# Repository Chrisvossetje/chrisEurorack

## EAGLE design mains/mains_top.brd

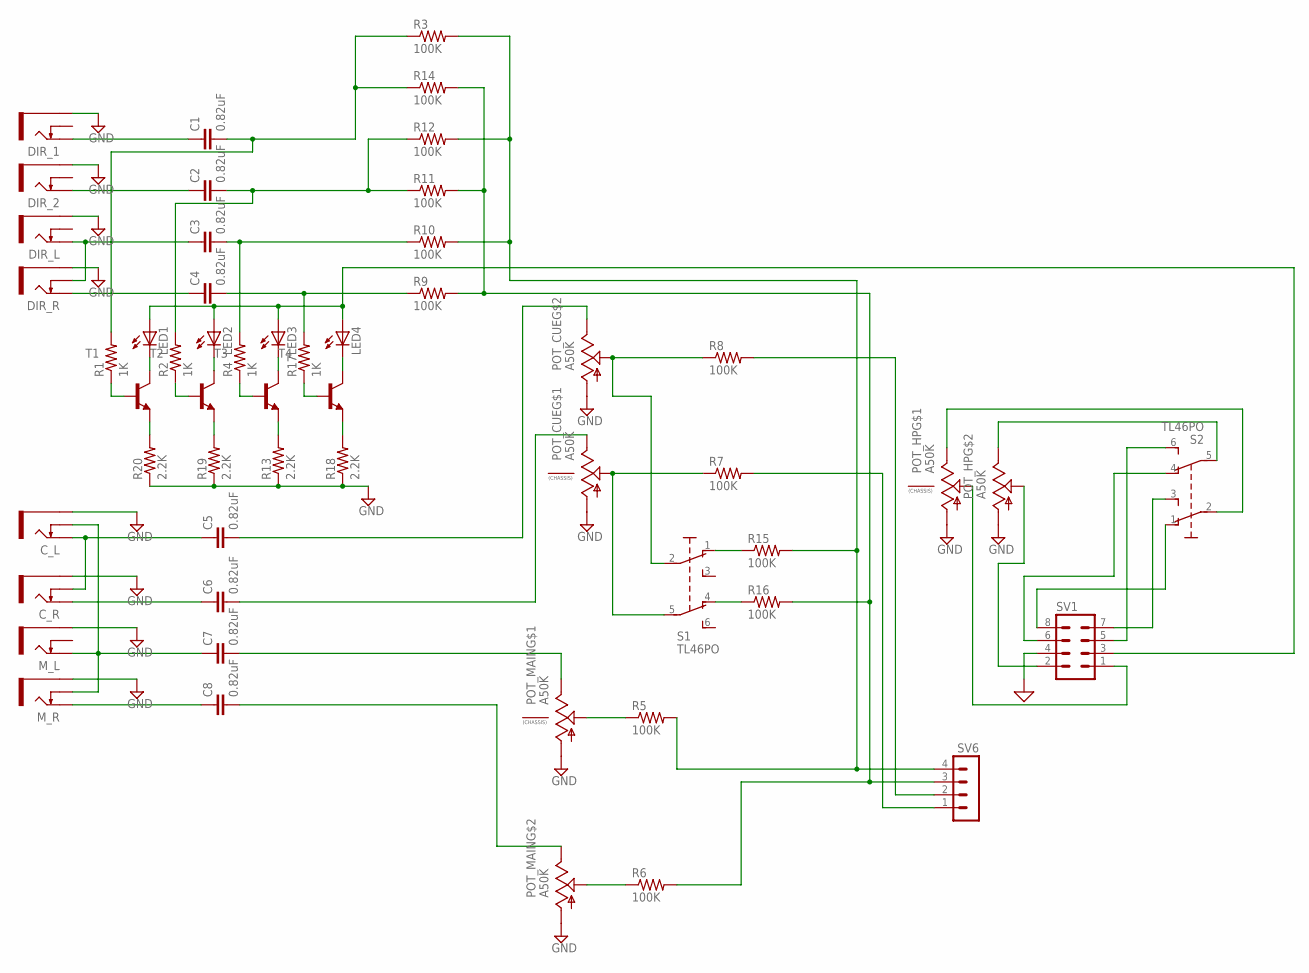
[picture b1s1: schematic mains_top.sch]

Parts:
C1, C2, C3, C4, C5, C6, C7, C8: 0.82uF; C0603K
C_L: THONKICONNNEW; WQP-PJ301M-12_JACK
C_R: THONKICONNNEW; WQP-PJ301M-12_JACK
DIR_1, DIR_2: THONKICONNNEW; WQP-PJ301M-12_JACK
DIR_L: THONKICONNNEW; WQP-PJ301M-12_JACK
DIR_R: THONKICONNNEW; WQP-PJ301M-12_JACK
LED1, LED2, LED3, LED4: LED3MM
M_L: THONKICONNNEW; WQP-PJ301M-12_JACK
M_R: THONKICONNNEW; WQP-PJ301M-12_JACK
POT_CUE: A50K; DUAL_9MM_SNAP-IN_POT
POT_HP: A50K; DUAL_9MM_SNAP-IN_POT
POT_MAIN: A50K; DUAL_9MM_SNAP-IN_POT
R1, R2, R4, R17: 1K; R0603
R3, R5, R6, R7, R8, R9, R10, R11, R12, R14, R15, R16: 100K; R0603
R13, R18, R19, R20: 2.2K; R0603
S1, S2: TL46PO; TL4XPO
SV1: MA04-2
SV6: MA04-1
T1, T2, T3, T4: MMBT3904LT1-NPN-SOT23-BEC; SOT23-BEC

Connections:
GND: C_L.P$3_SLEEVE (SLEEVE), C_R.P$3_SLEEVE (SLEEVE), DIR_1.P$3_SLEEVE (SLEEVE), DIR_2.P$3_SLEEVE (SLEEVE), DIR_L.P$3_SLEEVE (SLEEVE), DIR_R.P$3_SLEEVE (SLEEVE), M_L.P$3_SLEEVE (SLEEVE), M_R.P$3_SLEEVE (SLEEVE), POT_CUE.1 (A), POT_CUE.1B (A), POT_HP.1 (A), POT_HP.1B (A), POT_MAIN.1 (A), POT_MAIN.1B (A), R13.1, R18.1, R19.1, R20.1, SV1.4
unnamed: S2.1 (O), SV1.8
unnamed: R20.2, T1.E
unnamed: R19.2, T2.E
unnamed: S2.4 (O1), SV1.6
unnamed: LED1.K (C), T1.C
unnamed: POT_HP.2B (S), SV1.2
unnamed: C7.1, C_L.P$2_SWITCH (SWITCH), M_L.P$1_TIP (TIP), M_R.P$2_SWITCH (SWITCH)
unnamed: POT_HP.2 (S), SV1.1
unnamed: R1.1, T1.B
unnamed: R2.1, T2.B
unnamed: LED1.A, LED2.A, LED3.A, LED4.A, SV1.3
unnamed: C8.2, POT_MAIN.3B (E)
unnamed: C3.2, R4.2, R10.1
unnamed: C4.2, R9.1, R17.2
unnamed: C2.1, DIR_2.P$1_TIP (TIP)
unnamed: C1.1, DIR_1.P$1_TIP (TIP)
unnamed: C6.2, POT_CUE.3 (E)
unnamed: C5.2, POT_CUE.3B (E)
unnamed: POT_CUE.2B (S), R8.1, S1.2
unnamed: LED3.K (C), T3.C
unnamed: POT_MAIN.2 (S), R5.1
unnamed: POT_MAIN.2B (S), R6.1
unnamed: S2.6 (S1), SV1.5
unnamed: LED4.K (C), T4.C
unnamed: S2.3 (S), SV1.7
unnamed: R17.1, T4.B
unnamed: POT_HP.3B (E), S2.5 (P1)
unnamed: POT_HP.3 (E), S2.2
unnamed: R15.1, S1.1 (O)
unnamed: R16.1, S1.4 (O1)
unnamed: R6.2, R9.2, R11.2, R14.2, R16.2, SV6.3
unnamed: R4.1, T3.B
unnamed: R7.2, SV6.1
unnamed: R8.2, SV6.2
unnamed: LED2.K (C), T2.C
unnamed: R13.2, T3.E
unnamed: R18.2, T4.E
unnamed: POT_CUE.2 (S), R7.1, S1.5 (P1)
unnamed: C3.1, DIR_L.P$1_TIP (TIP), DIR_R.P$2_SWITCH (SWITCH)
unnamed: C2.2, R2.2, R11.1, R12.1
unnamed: C1.2, R1.2, R3.1, R14.1
unnamed: C4.1, DIR_R.P$1_TIP (TIP)
unnamed: C7.2, POT_MAIN.3 (E)
unnamed: C5.1, C_L.P$1_TIP (TIP), C_R.P$2_SWITCH (SWITCH)
unnamed: C8.1, M_R.P$1_TIP (TIP)
unnamed: C6.1, C_R.P$1_TIP (TIP)
unnamed: R3.2, R5.2, R10.2, R12.2, R15.2, SV6.4

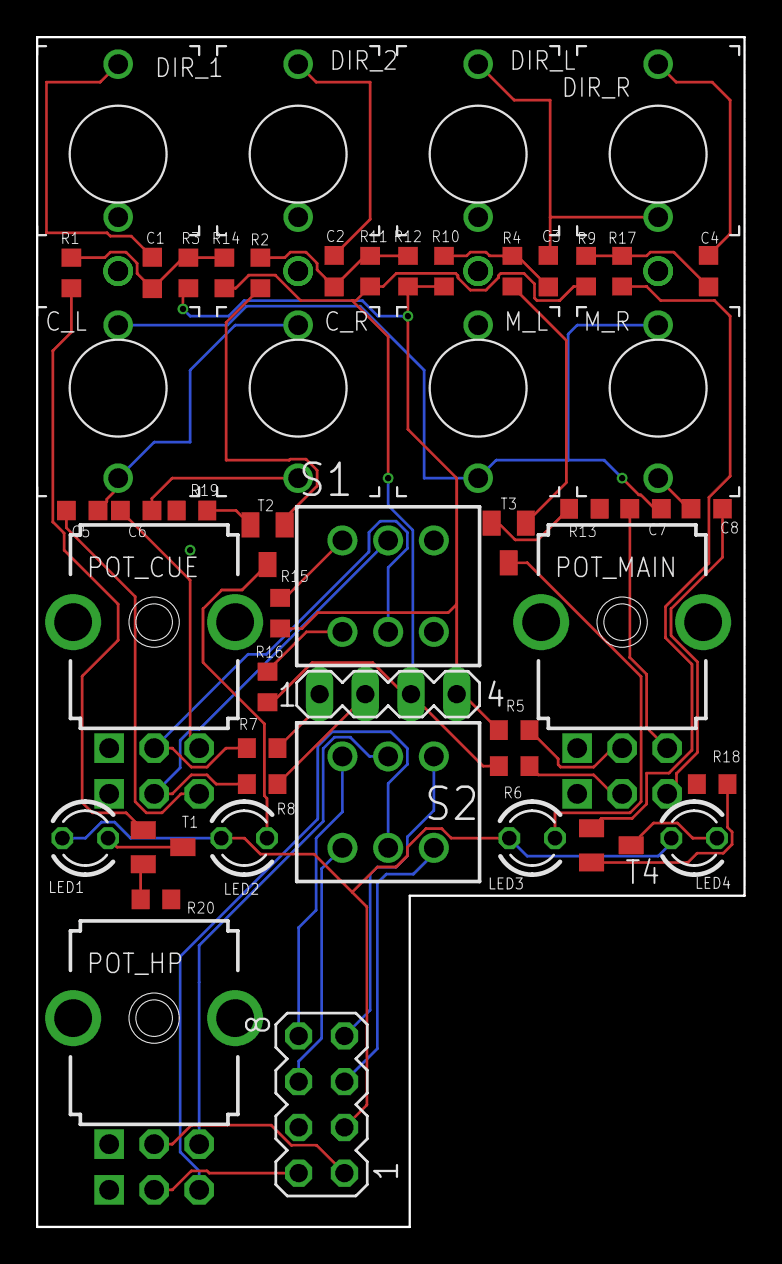
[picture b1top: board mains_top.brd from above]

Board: 2 copper layers, 39.3 x 66.1 mm, 51 parts (0 on the bottom side), 48 nets.

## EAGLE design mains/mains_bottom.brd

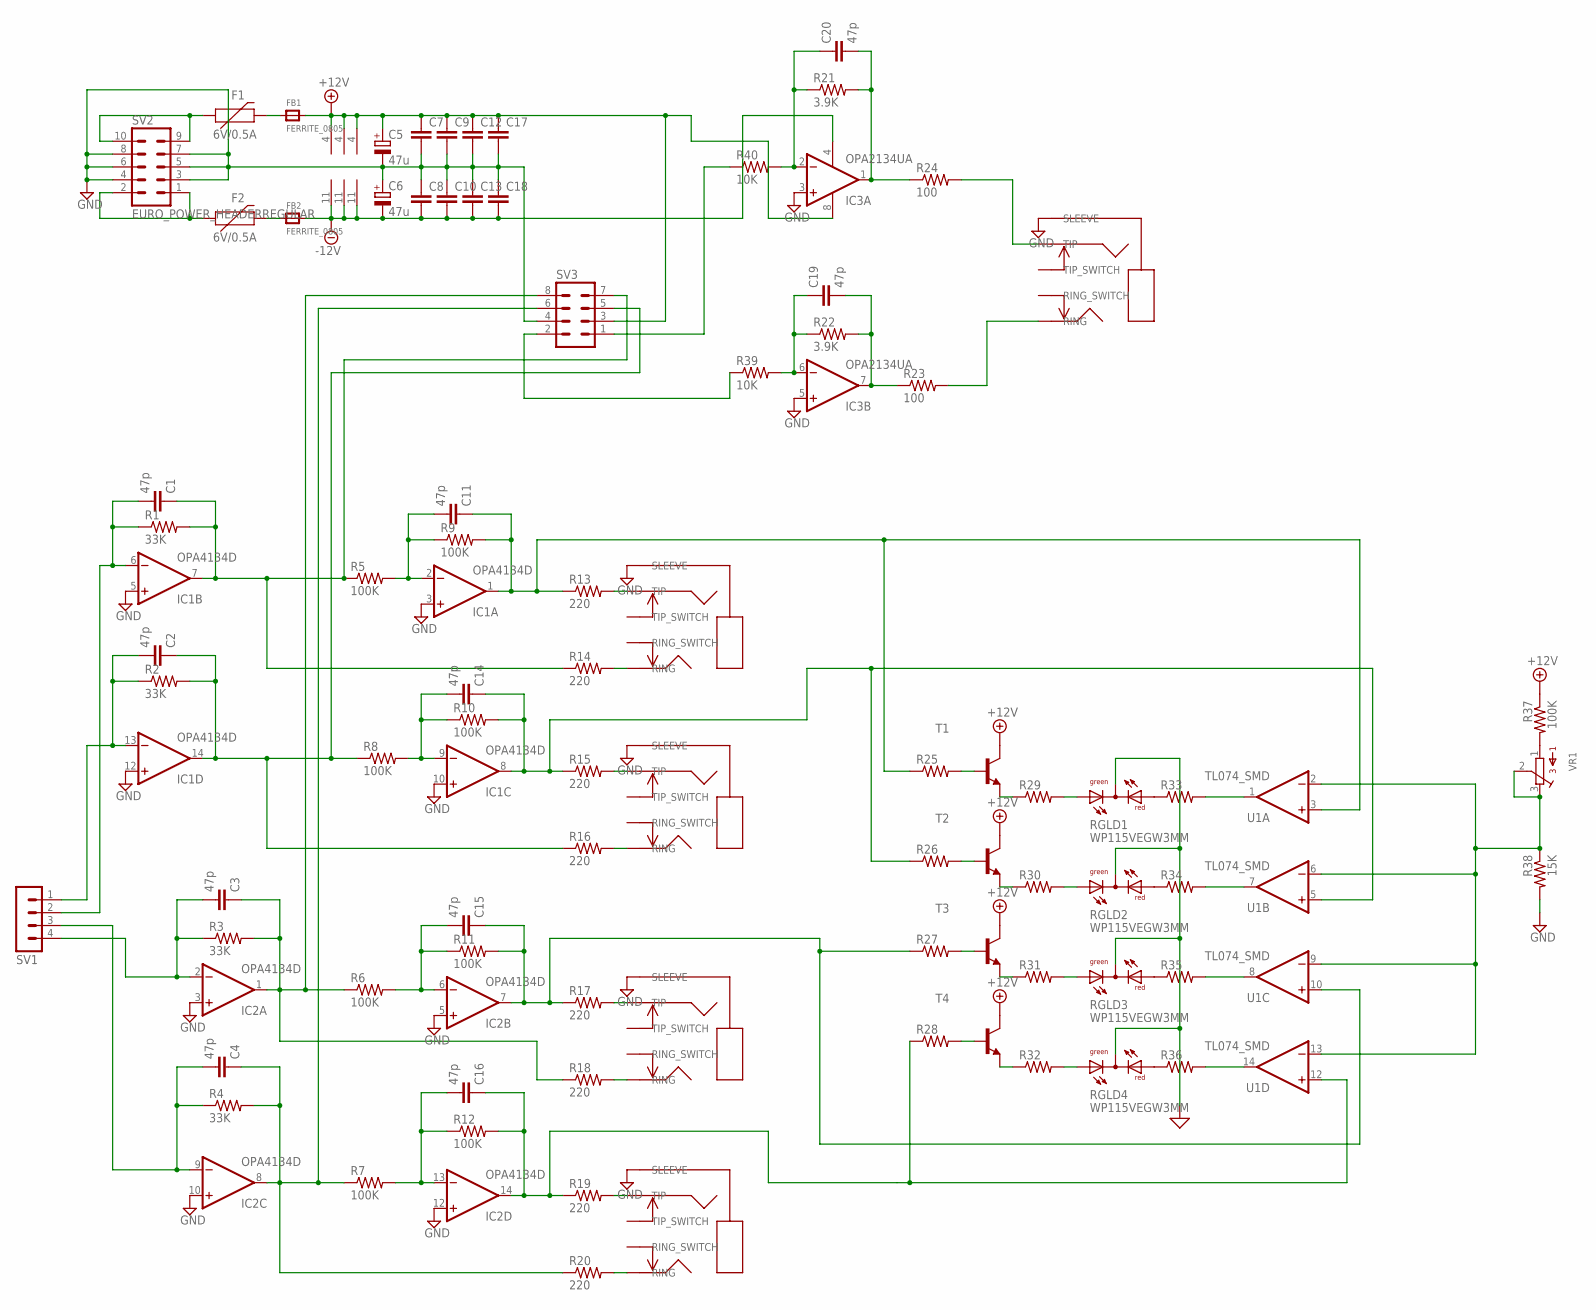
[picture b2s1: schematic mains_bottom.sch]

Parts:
C1, C2, C3, C4, C11, C14, C15, C16, C19, C20: 47p; C0603K
C5, C6: 47u; PANASONIC_D
C7, C8, C9, C10, C12, C13, C17, C18: C-EUC0603; C0603
C_L: WQP-PJ612A; JACK
C_R: WQP-PJ612A; JACK
F1, F2: 6V/0.5A; 1206
FB1, FB2: FERRITE_0805; _0805
IC1, IC2: OPA4134D; SO14
IC3: OPA2134UA; SO08
M_L: WQP-PJ612A; JACK
M_R: WQP-PJ612A; JACK
PHONES: WQP-PJ612A; JACK
R1, R2, R3, R4: 33K; R0603
R5, R6, R7, R8, R9, R10, R11, R12, R37: 100K; R0603
R13, R14, R15, R16, R17, R18, R19, R20: 220; R0603
R21, R22: 3.9K; R0603
R23, R24: 100; R0603
R25, R26, R27, R28, R29, R30, R31, R32, R33, R34, R35, R36: R-US_R0603; R0603
R38: 15K; R0603
R39, R40: 10K; R0603
RGLD1, RGLD2, RGLD3, RGLD4: WP115VEGW3MM; DUOLED-A-3MM
SV1: MA04-1
SV2: EURO_POWER_HEADERREGULAR; EURO_POWER_HEADER
SV3: MA04-2
T1, T2, T3, T4: BC817-40-NPN-SOT23-BEC; SOT23-BEC
U1: TL074_SMD; SO14
VR1: BOURNS_3362P_TRIMMERP; BOURNS_3362P_TRIMMER

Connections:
+12V: C5.+, C7.1, C9.1, C12.1, C17.1, FB1.2, IC1.4 (V+), IC2.4 (V+), IC3.8 (V+), R37.1, SV3.3, T1.C, T2.C, T3.C, T4.C, U1.4 (V+)
-12V: C6.-, C8.2, C10.2, C13.2, C18.2, FB2.2, IC1.11 (V-), IC2.11 (V-), IC3.4 (V-), U1.11 (V-)
GND: C5.-, C6.+, C7.2, C8.1, C9.2, C10.1, C12.2, C13.1, C17.2, C18.1, C_L.PIN1 (SLEEVE), C_R.PIN1 (SLEEVE), IC1.3 (+IN), IC1.5 (+IN), IC1.10 (+IN), IC1.12 (+IN), IC2.3 (+IN), IC2.5 (+IN), IC2.10 (+IN), IC2.12 (+IN), IC3.3 (+IN), IC3.5 (+IN), M_L.PIN1 (SLEEVE), M_R.PIN1 (SLEEVE), PHONES.PIN1 (SLEEVE), R38.2, RGLD1.2 (C), RGLD2.2 (C), RGLD3.2 (C), RGLD4.2 (C), SV2.3, SV2.4, SV2.5, SV2.6, SV2.7, SV2.8, SV3.4
unnamed: C19.1, IC3.6 (-IN), R22.1, R39.2
unnamed: C20.1, IC3.2 (-IN), R21.1, R40.2
unnamed: C3.1, IC2.1 (OUT), R3.2, R6.1, R18.1, SV3.8
unnamed: C4.1, IC2.8 (OUT), R4.2, R7.1, R20.1, SV3.6
unnamed: R32.1, T4.E
unnamed: C1.1, IC1.7 (OUT), R1.2, R5.1, R14.1, SV3.7
unnamed: C3.2, IC2.2 (-IN), R3.1, SV1.4
unnamed: R27.2, T3.B
unnamed: R30.1, T2.E
unnamed: R29.1, T1.E
unnamed: R33.1, RGLD1.1 (AR)
unnamed: R34.1, RGLD2.1 (AR)
unnamed: R35.1, RGLD3.1 (AR)
unnamed: R36.1, RGLD4.1 (AR)
unnamed: R36.2, U1.14 (OUT)
unnamed: R29.2, RGLD1.3 (AG)
unnamed: R30.2, RGLD2.3 (AG)
unnamed: R31.2, RGLD3.3 (AG)
unnamed: C4.2, IC2.9 (-IN), R4.1, SV1.3
unnamed: R39.1, SV3.2
unnamed: C15.1, IC2.7 (OUT), R11.2, R17.1, R27.1, U1.10 (+IN)
unnamed: C14.1, IC1.8 (OUT), R10.2, R15.1, R26.1, U1.5 (+IN)
unnamed: C2.2, IC1.13 (-IN), R2.1, SV1.1
unnamed: C1.2, IC1.6 (-IN), R1.1, SV1.2
unnamed: C11.1, IC1.1 (OUT), R9.2, R13.1, R25.1, U1.3 (+IN)
unnamed: C16.1, IC2.14 (OUT), R12.2, R19.1, R28.1, U1.12 (+IN)
unnamed: C_L.PIN3 (TIP), R13.2
unnamed: C_L.PIN2 (RING), R14.2
unnamed: C_R.PIN3 (TIP), R15.2
unnamed: C_R.PIN2 (RING), R16.2
unnamed: M_L.PIN3 (TIP), R17.2
unnamed: M_L.PIN2 (RING), R18.2
unnamed: M_R.PIN3 (TIP), R19.2
unnamed: M_R.PIN2 (RING), R20.2
unnamed: C2.1, IC1.14 (OUT), R2.2, R8.1, R16.1, SV3.5
unnamed: PHONES.PIN3 (TIP), R24.2
unnamed: PHONES.PIN2 (RING), R23.2
unnamed: C19.2, IC3.7 (OUT), R22.2, R23.1
unnamed: C20.2, IC3.1 (OUT), R21.2, R24.1
unnamed: R40.1, SV3.1
unnamed: R35.2, U1.8 (OUT)
unnamed: R34.2, U1.7 (OUT)
unnamed: R33.2, U1.1 (OUT)
unnamed: R32.2, RGLD4.3 (AG)
unnamed: R28.2, T4.B
unnamed: R31.1, T3.E
unnamed: F2.1, SV2.1, SV2.2
unnamed: F1.1, SV2.9, SV2.10
unnamed: R37.2, VR1.1
unnamed: R38.1, U1.2 (-IN), U1.6 (-IN), U1.9 (-IN), U1.13 (-IN), VR1.2, VR1.3
unnamed: F2.2, FB2.1
unnamed: F1.2, FB1.1
unnamed: R26.2, T2.B
unnamed: R25.2, T1.B
unnamed: C11.2, IC1.2 (-IN), R5.2, R9.1
unnamed: C14.2, IC1.9 (-IN), R8.2, R10.1
unnamed: C15.2, IC2.6 (-IN), R6.2, R11.1
unnamed: C16.2, IC2.13 (-IN), R7.2, R12.1

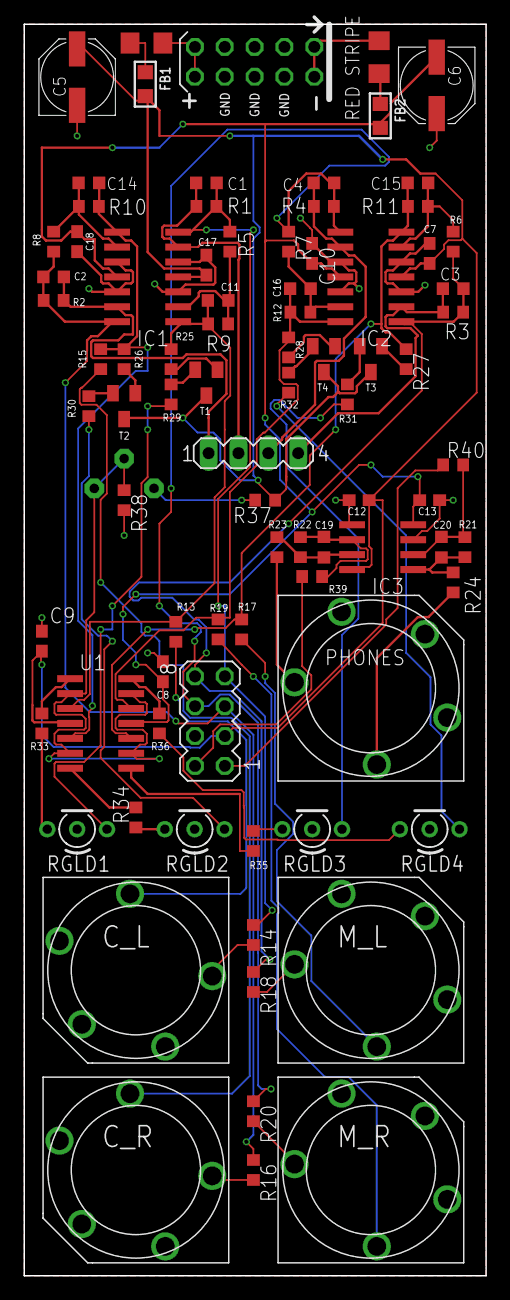
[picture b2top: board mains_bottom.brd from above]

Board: 2 copper layers, 39.3 x 106.5 mm, 85 parts (1 on the bottom side), 61 nets.

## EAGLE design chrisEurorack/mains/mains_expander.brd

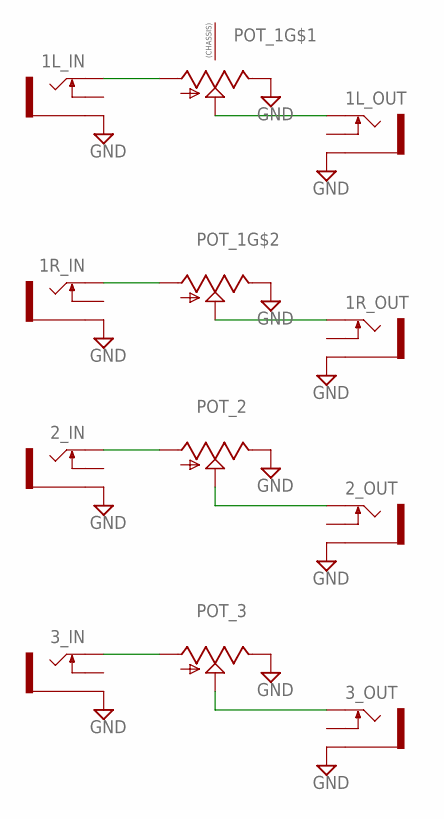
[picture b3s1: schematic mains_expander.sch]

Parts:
1L_IN, 1L_OUT, 1R_IN, 1R_OUT, 2_IN, 2_OUT, 3_IN, 3_OUT: THONKICONNNEW; WQP-PJ301M-12_JACK
POT_1: ALPHA-9MM-DUALPOT; DUAL_9MM_SNAP-IN_POT
POT_2, POT_3: 9MM_SNAP-IN_POT_; 9MM_SNAP-IN_POT

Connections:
GND: 1L_IN.P$3_SLEEVE (SLEEVE), 1L_OUT.P$3_SLEEVE (SLEEVE), 1R_IN.P$3_SLEEVE (SLEEVE), 1R_OUT.P$3_SLEEVE (SLEEVE), 2_IN.P$3_SLEEVE (SLEEVE), 2_OUT.P$3_SLEEVE (SLEEVE), 3_IN.P$3_SLEEVE (SLEEVE), 3_OUT.P$3_SLEEVE (SLEEVE), POT_1.3 (E), POT_1.3B (E), POT_2.3 (E), POT_3.3 (E)
unnamed: 2_IN.P$1_TIP (TIP), POT_2.1 (A)
unnamed: 3_IN.P$1_TIP (TIP), POT_3.1 (A)
unnamed: 1R_IN.P$1_TIP (TIP), POT_1.1B (A)
unnamed: 1L_IN.P$1_TIP (TIP), POT_1.1 (A)
unnamed: 1L_OUT.P$1_TIP (TIP), POT_1.2 (S)
unnamed: 2_OUT.P$1_TIP (TIP), POT_2.2 (S)
unnamed: 1R_OUT.P$1_TIP (TIP), POT_1.2B (S)
unnamed: 3_OUT.P$1_TIP (TIP), POT_3.2 (S)

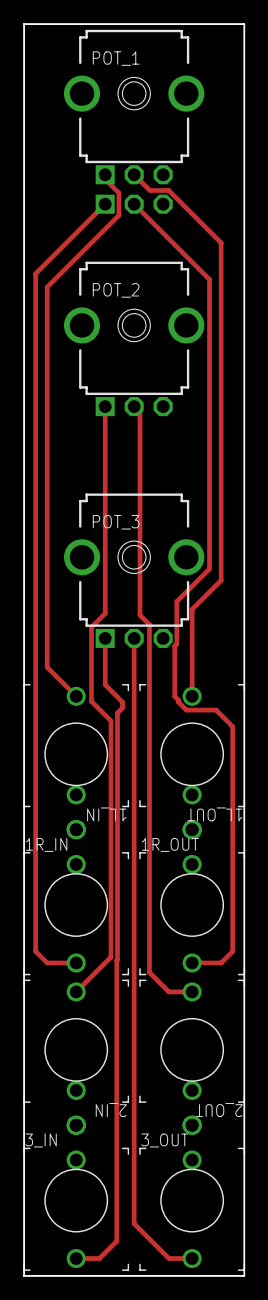
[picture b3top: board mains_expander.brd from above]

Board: 2 copper layers, 19.0 x 108.0 mm, 11 parts (0 on the bottom side), 9 nets.

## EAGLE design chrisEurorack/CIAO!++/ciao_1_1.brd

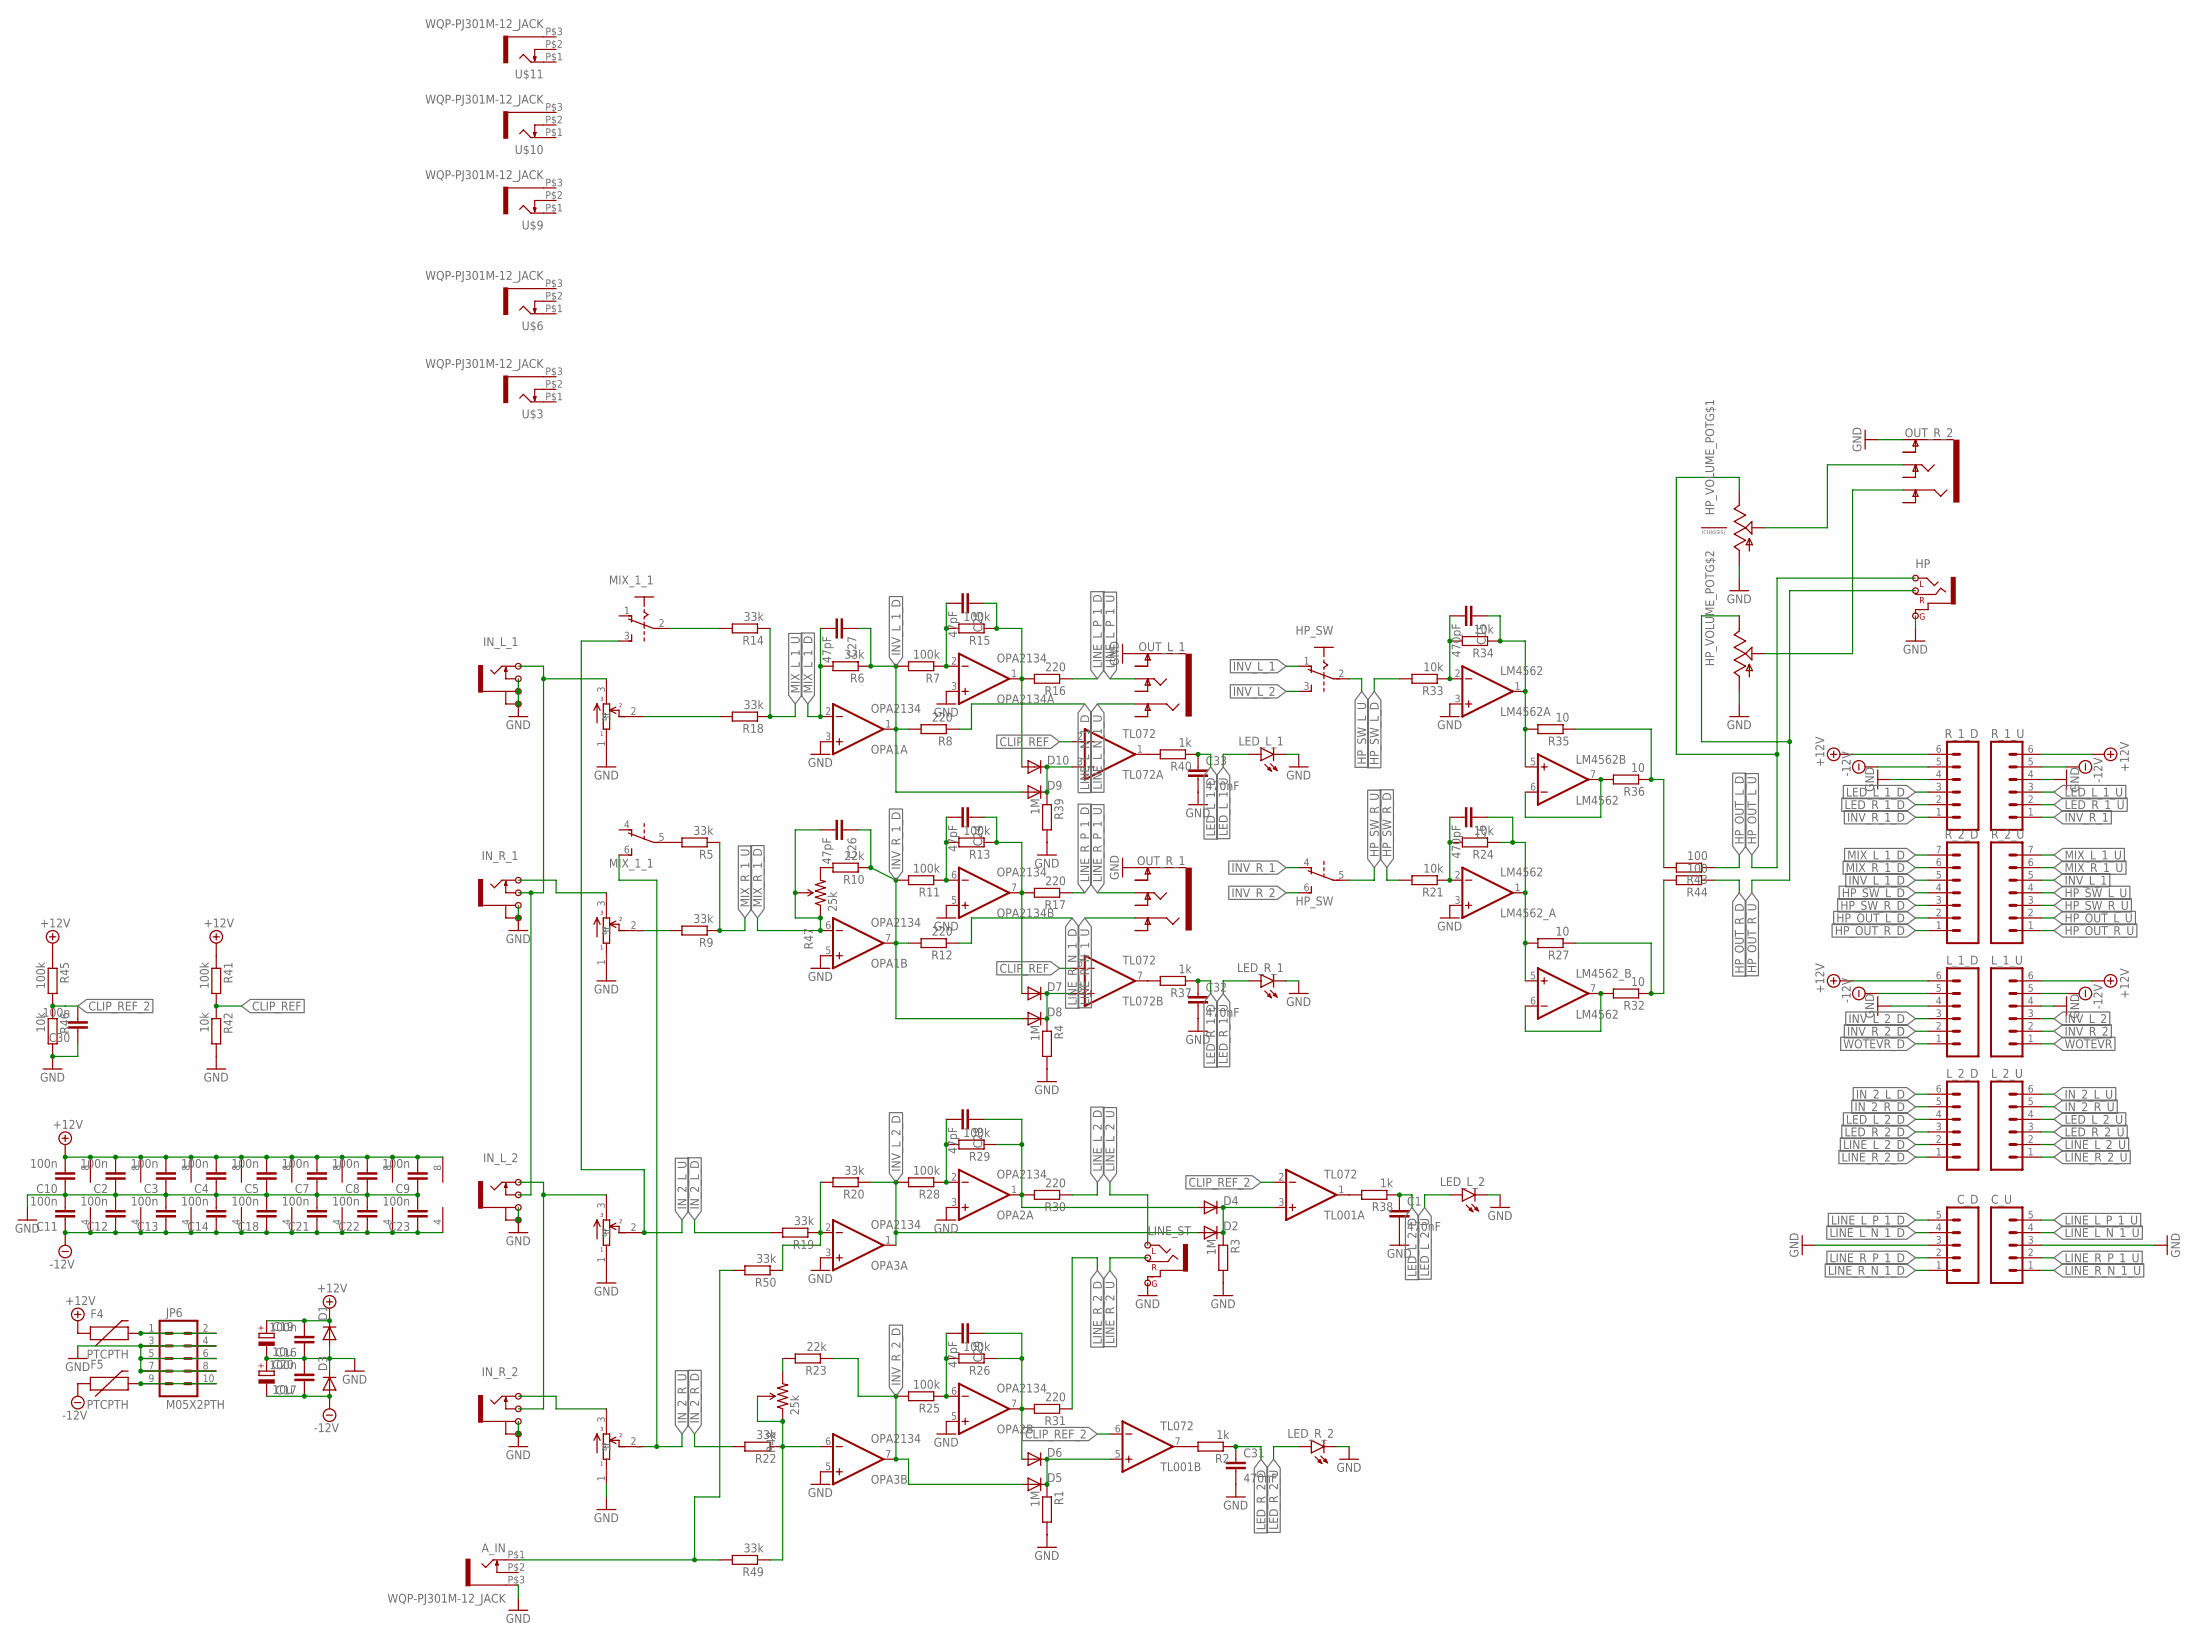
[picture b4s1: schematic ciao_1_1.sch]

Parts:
A_IN: WQP-PJ301M-12_JACK
C1, C31, C32, C33: 470nF; C050-024X044
C2, C3, C4, C5, C7, C8, C9, C10, C11, C12, C13, C14, C16, C17, C18, C21, C22, C23, C30: 100n; C050-024X044
C6, C15: 470pF; C050-024X044
C19, C20: 10u; E2-5
C24, C25, C26, C27, C28, C29: 47pF; C050-024X044
CH_1_POT, CH_2_POT: POTAK_DUAL
C_D: M05PTH; 1X05
C_U: M05PTH; 1X05
D1, D3: DIODE-D-7.5; D-7.5
D2, D4, D5, D6, D7, D8, D9, D10: DIODE-D-5; D-5
F4, F5: PTCPTH; PTC
HP: STEREO
HP_SW: A68-A31
HP_VOLUME_POT: ALPHA-9MM-DUALPOT; DUAL_9MM_SNAP-IN_POT
IN_L_1, IN_L_2: PJ-301BMB; PJ-301BM-B
IN_R_1, IN_R_2: PJ-301BMB; PJ-301BM-B
JP6: M05X2PTH; AVR_ICSP
LED_L_1, LED_L_2: LED3MM
LED_R_1, LED_R_2: LED3MM
LINE_ST: STEREO
LM4562, LM4562_: LM4562; DIL08
L_1_D, L_1_U, L_2_D, L_2_U: M06NO_SILK; 1X06_NO_SILK
MIX_1_1: A68-A31
OPA1, OPA2, OPA3, OPA2134: OPA2134; DIL08
OUT_L_1: AUDIO-JACK4-.25-HORIZ-TRS; AUDIO-JACK-.25-INCH-HORIZ-PTH
OUT_R_1, OUT_R_2: AUDIO-JACK4-.25-HORIZ-TRS; AUDIO-JACK-.25-INCH-HORIZ-PTH
R1, R3, R4, R39: 1M; 0204/5
R2, R37, R38, R40: 1k; 0204/5
R5, R6, R9, R14, R18, R19, R20, R22, R49, R50: 33k; 0204/5
R7, R11, R13, R15, R25, R26, R28, R29, R41, R45: 100k; 0204/5
R8, R12, R16, R17, R30, R31: 220; 0204/5
R10, R23: 22k; 0204/5
R21, R24, R33, R34, R42, R46: 10k; 0204/5
R27, R32, R35, R36: 10; 0204/5
R43, R44: 100; 0204/5
R47, R48: 25k; TRIM_POT_PTH_STAND
R_1_D, R_1_U: M06NO_SILK; 1X06_NO_SILK
R_2_D, R_2_U: M07; 1X07
TL001, TL072: TL072; DIL08
U$3, U$6, U$9, U$10, U$11: WQP-PJ301M-12_JACK

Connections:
+12V: C2.2, C3.2, C4.2, C5.2, C7.2, C8.2, C9.2, C10.2, C16.2, C19.+, D1.C, F4.P$1 (1), LM4562.8 (V+), LM4562_.8 (V+), L_1_D.6, L_1_U.6, OPA1.8 (V+), OPA2.8 (V+), OPA3.8 (V+), OPA2134.8 (V+), R41.1, R45.1, R_1_D.6, R_1_U.6, TL001.8 (V+), TL072.8 (V+)
-12V: C11.1, C12.1, C13.1, C14.1, C17.1, C18.1, C20.-, C21.1, C22.1, C23.1, D3.A, F5.P$1 (1), LM4562.4 (V-), LM4562_.4 (V-), L_1_D.5, L_1_U.5, OPA1.4 (V-), OPA2.4 (V-), OPA3.4 (V-), OPA2134.4 (V-), R_1_D.5, R_1_U.5, TL001.4 (V-), TL072.4 (V-)
CLIP_REF: R41.2, R42.1, TL072.2 (-IN), TL072.6 (-IN)
CLIP_REF_2: C30.2, R45.2, R46.1, TL001.2 (-IN), TL001.6 (-IN)
CLIP_REF_ADFPOASH: D5.C, D6.C, R1.1, TL001.5 (+IN)
GND: A_IN.P$3 (1), C1.2, C2.1, C3.1, C4.1, C5.1, C7.1, C8.1, C9.1, C10.1, C11.2, C12.2, C13.2, C14.2, C16.1, C17.2, C18.2, C19.-, C20.+, C21.2, C22.2, C23.2, C30.1, C31.2, C32.2, C33.2, CH_1_POT.1, CH_1_POT.1_ (1), CH_2_POT.1, CH_2_POT.1_ (1), C_D.3, C_U.3, D1.A, D3.C, HP.GND (G), HP_VOLUME_POT.1 (A), HP_VOLUME_POT.1B (A), IN_L_1.G1, IN_L_1.G2, IN_L_1.SW, IN_L_2.G1, IN_L_2.G2, IN_R_1.G1, IN_R_1.G2, IN_R_2.G1, IN_R_2.G2, JP6.3, JP6.4, JP6.5, JP6.6, JP6.7, JP6.8, LED_L_1.K (C), LED_L_2.K (C), LED_R_1.K (C), LED_R_2.K (C), LINE_ST.GND (G), LM4562.3 (+IN), LM4562_.3 (+IN), L_1_D.4, L_1_U.4, OPA1.3 (+IN), OPA1.5 (+IN), OPA2.3 (+IN), OPA2.5 (+IN), OPA3.3 (+IN), OPA3.5 (+IN), OPA2134.3 (+IN), OPA2134.5 (+IN), OUT_L_1.P$2 (EARTH), OUT_R_1.P$2 (EARTH), OUT_R_2.P$2 (EARTH), R1.2, R3.2, R4.2, R39.2, R42.2, R46.2, R_1_D.4, R_1_U.4
HP_OUT_L_D: R43.1, R_2_D.2
HP_OUT_L_U: HP.LEFT_ (L), HP_VOLUME_POT.3 (E), R_2_U.2
HP_OUT_R_D: R44.1, R_2_D.1
HP_OUT_R_U: HP.RIGHT_ (R), HP_VOLUME_POT.3B (E), R_2_U.1
HP_SW_L_D: R33.2, R_2_D.4
HP_SW_L_U: HP_SW.2, R_2_U.4
HP_SW_R_D: R21.2, R_2_D.3
HP_SW_R_U: HP_SW.5, R_2_U.3
INV_L_1: HP_SW.1 (O), R_2_U.5
INV_L_1_D: C27.1, D9.A, OPA1.1 (OUT), R6.1, R7.2, R8.2, R_2_D.5
INV_L_2: HP_SW.3 (S), L_1_U.3
INV_L_2_D: D2.A, L_1_D.3, OPA3.1 (OUT), R20.1, R28.2
INV_R_1: HP_SW.4 (O), R_1_U.1
INV_R_1_D: C26.1, D8.A, OPA1.7 (OUT), R10.1, R11.2, R12.2, R_1_D.1
INV_R_2: HP_SW.6 (S), L_1_U.2
INV_R_2_D: D5.A, L_1_D.2, OPA3.7 (OUT), R23.1, R25.2
IN_2_L_D: L_2_D.6, R19.2
IN_2_L_U: CH_2_POT.2, L_2_U.6, MIX_1_1.3 (S)
IN_2_R_D: L_2_D.5, R22.2
IN_2_R_U: CH_2_POT.2_ (2), L_2_U.5, MIX_1_1.6 (S)
LED_L_1_D: C33.1, R40.1, R_1_D.3
LED_L_1_U: LED_L_1.A, R_1_U.3
LED_L_2_D: C1.1, L_2_D.4, R38.1
LED_L_2_U: LED_L_2.A, L_2_U.4
LED_R_1_D: C32.1, R37.1, R_1_D.2
LED_R_1_U: LED_R_1.A, R_1_U.2
LED_R_2_D: C31.1, L_2_D.3, R2.1
LED_R_2_U: LED_R_2.A, L_2_U.3
LINE_L_2_D: L_2_D.2, R30.1
LINE_L_2_U: LINE_ST.LEFT_ (L), L_2_U.2
LINE_L_N_1_D: C_D.4, R8.1
LINE_L_N_1_U: C_U.4, OUT_L_1.P$4 (RING)
LINE_L_P_1_D: C_D.5, R16.1
LINE_L_P_1_U: C_U.5, OUT_L_1.P$6 (TIP)
LINE_R_2_D: L_2_D.1, R31.1
LINE_R_2_U: LINE_ST.RIGHT_ (R), L_2_U.1
LINE_R_N_1_D: C_D.1, R12.1
LINE_R_N_1_U: C_U.1, OUT_R_1.P$4 (RING)
LINE_R_P_1_D: C_D.2, R17.1
LINE_R_P_1_U: C_U.2, OUT_R_1.P$6 (TIP)
MIX_L_1_D: C27.2, OPA1.2 (-IN), R6.2, R_2_D.7
MIX_L_1_U: R14.1, R18.1, R_2_U.7
MIX_R_1_D: C26.2, OPA1.6 (-IN), R47.1 (CCW), R47.2 (WIPER), R_2_D.6
MIX_R_1_U: R5.1, R9.1, R_2_U.6
unnamed: R10.2, R47.3 (CW)
unnamed: CH_2_POT.3, IN_L_2.T, IN_R_2.SW
unnamed: R40.2, TL072.1 (OUT)
unnamed: CH_2_POT.3_ (3), IN_R_2.T
unnamed: C25.2, OPA2134.2 (-IN), R7.1, R15.2
unnamed: OPA3.6 (-IN), R22.1, R48.1 (CCW), R48.2 (WIPER), R49.1
unnamed: CH_1_POT.3_ (3), IN_R_1.T
unnamed: R23.2, R48.3 (CW)
unnamed: C25.1, D10.A, OPA2134.1 (OUT), R15.1, R16.2
unnamed: C24.2, OPA2134.6 (-IN), R11.1, R13.2
unnamed: A_IN.P$1 (2), R49.2, R50.2
unnamed: C24.1, D7.A, OPA2134.7 (OUT), R13.1, R17.2
unnamed: CH_1_POT.2_ (2), R9.2
unnamed: CH_1_POT.2, R18.2
unnamed: OPA3.2 (-IN), R19.1, R20.2, R50.1
unnamed: MIX_1_1.5, R5.2
unnamed: MIX_1_1.2, R14.2
unnamed: C29.2, OPA2.6 (-IN), R25.1, R26.2
unnamed: C29.1, D6.A, OPA2.7 (OUT), R26.1, R31.2
unnamed: C6.2, LM4562_.2 (-IN), R21.1, R24.2
unnamed: C28.2, OPA2.2 (-IN), R28.1, R29.2
unnamed: C28.1, D4.A, OPA2.1 (OUT), R29.1, R30.2
unnamed: C6.1, LM4562_.1 (OUT), LM4562_.5 (+IN), R24.1, R27.2
unnamed: LM4562_.6 (-IN), LM4562_.7 (OUT), R32.2
unnamed: R27.1, R32.1, R44.2
unnamed: C15.2, LM4562.2 (-IN), R33.1, R34.2
unnamed: C15.1, LM4562.1 (OUT), LM4562.5 (+IN), R34.1, R35.2
unnamed: LM4562.6 (-IN), LM4562.7 (OUT), R36.2
unnamed: R37.2, TL072.7 (OUT)
unnamed: R35.1, R36.1, R43.2
unnamed: D2.C, D4.C, R3.1, TL001.3 (+IN)
unnamed: CH_1_POT.3, IN_L_1.T, IN_L_2.SW, IN_R_1.SW
unnamed: F4.P$2 (2), JP6.1, JP6.2
unnamed: F5.P$2 (2), JP6.9, JP6.10
unnamed: R38.2, TL001.1 (OUT)
unnamed: D7.C, D8.C, R4.1, TL072.5 (+IN)
unnamed: R2.2, TL001.7 (OUT)
unnamed: D9.C, D10.C, R39.1, TL072.3 (+IN)
WOTEVR: L_1_U.1
WOTEVR_D: L_1_D.1

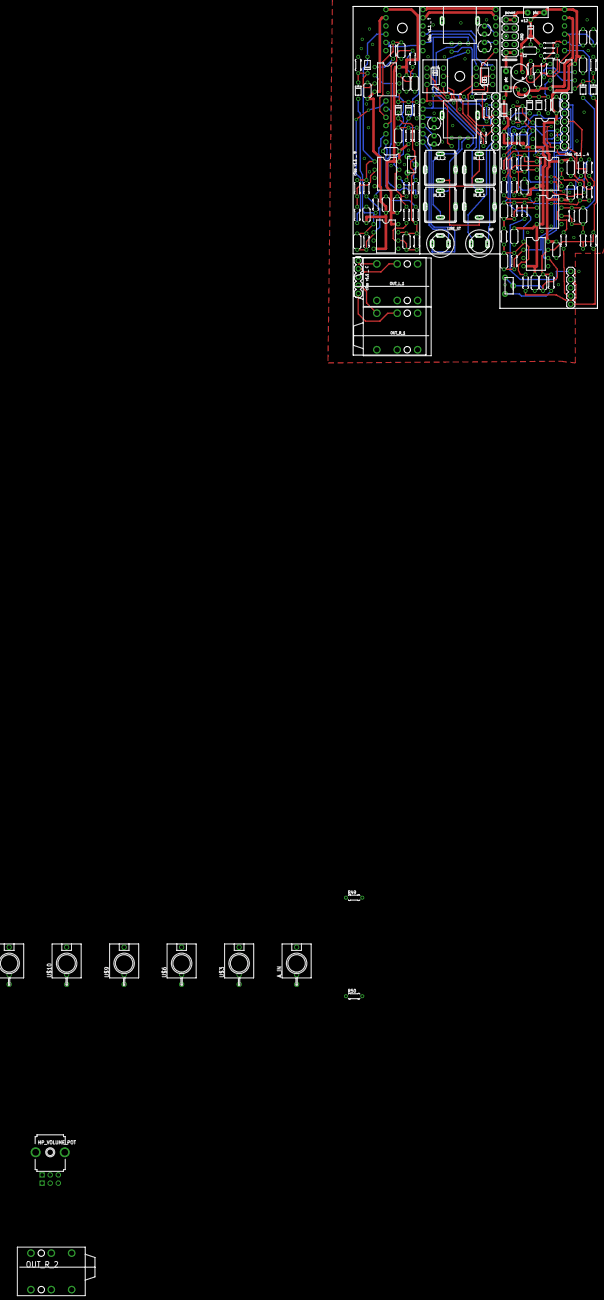
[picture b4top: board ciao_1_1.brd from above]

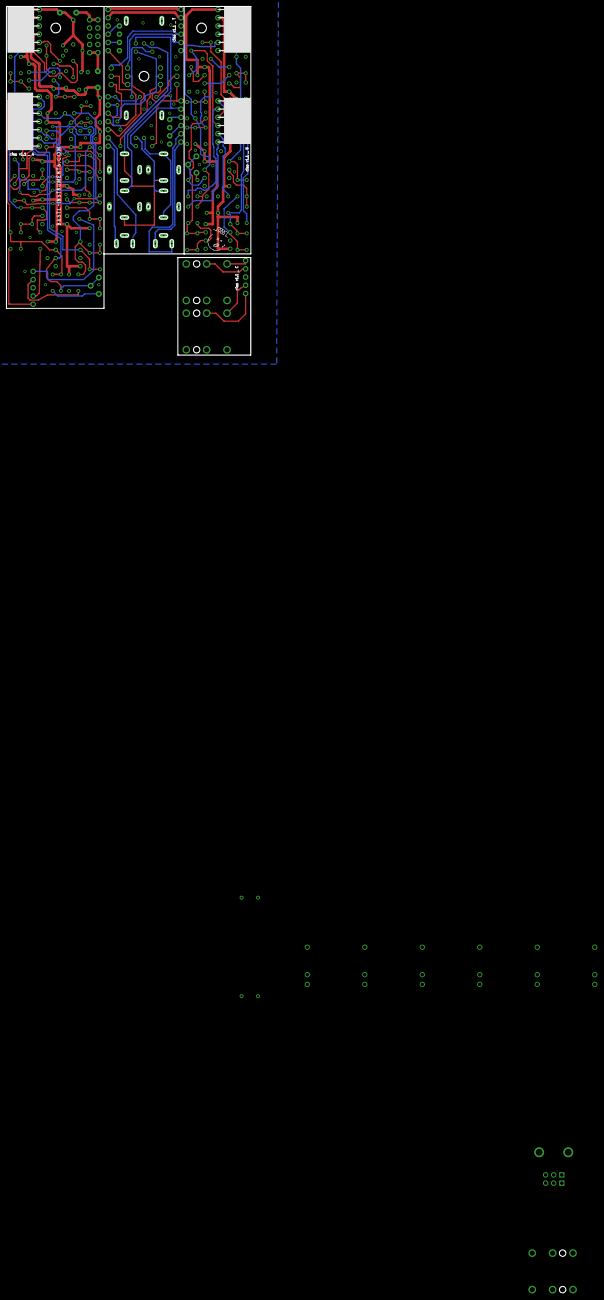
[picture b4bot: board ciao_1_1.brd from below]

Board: 2 copper layers, 75.6 x 93.3 mm, 143 parts (2 on the bottom side), 88 nets.

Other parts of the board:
U$2, U$7, U$8: 3,0
U$4: BASTL_WEB_2
U$5: BASTL_HLAVA_1

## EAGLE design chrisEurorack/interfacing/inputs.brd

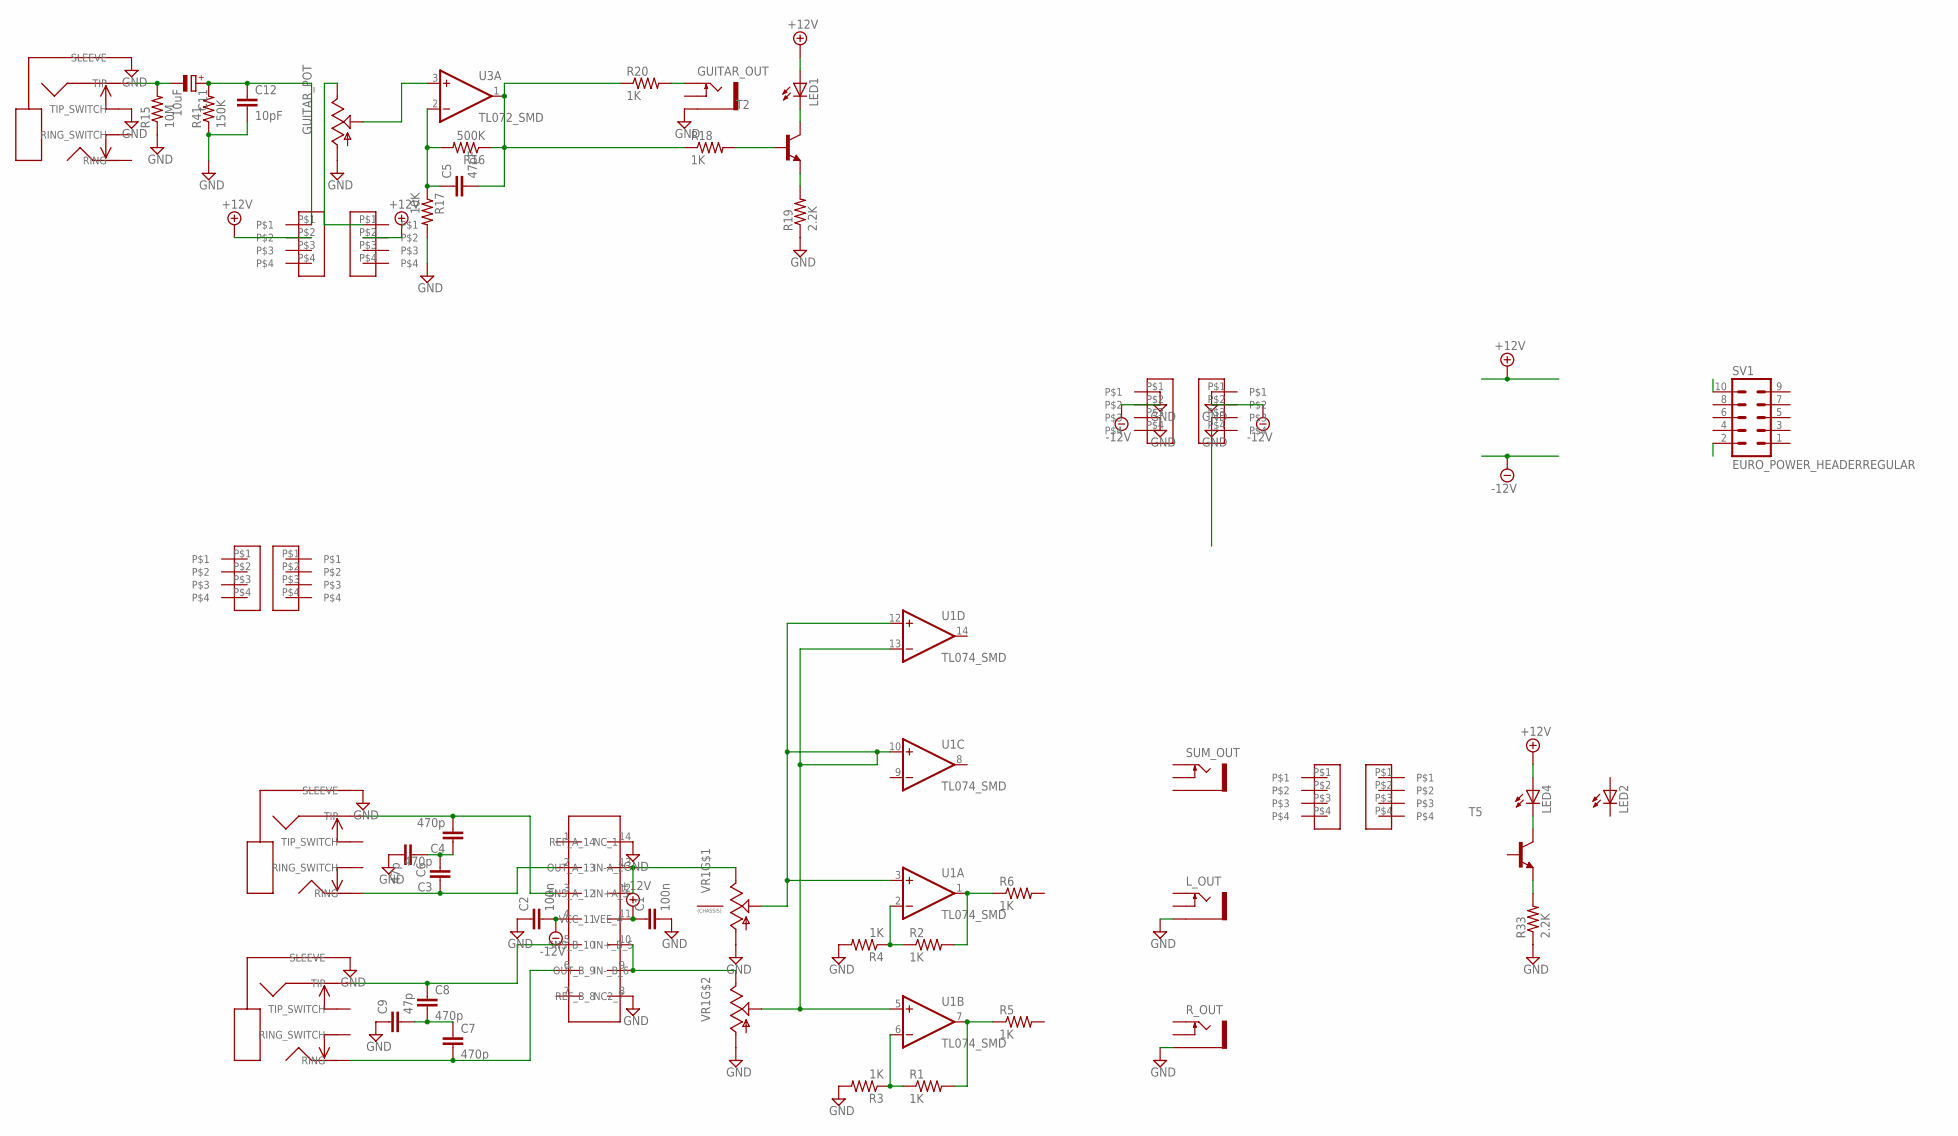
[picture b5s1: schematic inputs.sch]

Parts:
C1, C2: 100n; C0603
C3, C4, C7, C8: 470p; C0603
C5: 47pF; C0603
C6, C9: 47p; C0603
C11: 10uF; PANASONIC_B
C12: 10pF; C0603
GUITAR_INPUT: WQP-PJ612A; JACK
GUITAR_OUT: THONKICONNNEW; WQP-PJ301M-12_JACK
GUITAR_POT: 9MM_SNAP-IN_POT_; 9MM_SNAP-IN_POT
LB_B: 4PIN_HEADER; 4PIN
LB_O: 4PIN_HEADER; 4PIN
LED1, LED2, LED4: LED3MM
L_IN: WQP-PJ612A; JACK
L_OUT: THONKICONNNEW; WQP-PJ301M-12_JACK
R1, R2, R3, R4, R5, R6, R18, R20: 1K; R0603
R15: 10M; R0603
R16: 500K; R0603
R17: 10K; R0603
R19, R33: 2.2K; R0603
R41: 150K; R0603
R-IN: WQP-PJ612A; JACK
RB_B, RB_B1: 4PIN_HEADER; 4PIN
RB_O, RB_O1: 4PIN_HEADER; 4PIN
RO_B: 4PIN_HEADER; 4PIN
RO_O: 4PIN_HEADER; 4PIN
R_OUT: THONKICONNNEW; WQP-PJ301M-12_JACK
SUM_OUT: THONKICONNNEW; WQP-PJ301M-12_JACK
SV1: EURO_POWER_HEADERREGULAR; EURO_POWER_HEADER
T2, T5: MMBT3904LT1-NPN-SOT23-BEC; SOT23-BEC
U1: TL074_SMD; SO14
U3: TL072_SMD; SO08
U$1: THAT1280; SO-14
VR1: ALPHA-9MM-DUALPOT; DUAL_9MM_SNAP-IN_POT

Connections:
+12V: C1.1, LB_B.P$2, LB_O.P$2, LED1.A, LED4.A, U$1.11 (VCC_11)
-12V: C2.2, RB_B.P$2, RB_O.P$2, U$1.4 (VEE_4)
GND: C1.2, C2.1, C6.2, C9.1, C12.2, GUITAR_INPUT.PIN1 (SLEEVE), GUITAR_INPUT.PIN5 (TIP_SWITCH), GUITAR_OUT.P$3_SLEEVE (SLEEVE), GUITAR_POT.1 (A), L_IN.PIN1 (SLEEVE), L_OUT.P$3_SLEEVE (SLEEVE), R3.2, R4.2, R15.1, R17.2, R19.1, R33.1, R41.1, R-IN.PIN1 (SLEEVE), RB_B.P$1, RB_B.P$3, RB_O.P$1, RB_O.P$3, R_OUT.P$3_SLEEVE (SLEEVE), U$1.8 (REF_B_8), U$1.14 (REF_A_14), VR1.1 (A), VR1.1B (A)
unnamed: C4.2, L_IN.PIN3 (TIP), U$1.3 (IN+A_3)
unnamed: C11.-, GUITAR_INPUT.PIN3 (TIP), R15.2
unnamed: C11.+, C12.1, LB_O.P$1, R41.2
unnamed: U$1.9 (OUT_B_9), U$1.10 (SNS_B_10), VR1.3B (E)
unnamed: C8.1, R-IN.PIN3 (TIP), U$1.5 (IN+_B_5)
unnamed: C7.2, R-IN.PIN2 (RING), U$1.6 (IN-_B_6)
unnamed: C3.1, L_IN.PIN2 (RING), U$1.2 (IN-A_2)
unnamed: C7.1, C8.2, C9.2
unnamed: C3.2, C4.1, C6.1
unnamed: U$1.12 (SNS_A_12), U$1.13 (OUT_A_13), VR1.3 (E)
unnamed: R2.1, R4.1, U1.2 (-IN)
unnamed: U1.3 (+IN), U1.5 (+IN), U1.10 (+IN), U1.12 (+IN), U1.13 (-IN), VR1.2 (S), VR1.2B (S)
unnamed: R2.2, R6.1, U1.1 (OUT)
unnamed: R1.1, R3.1, U1.6 (-IN)
unnamed: R1.2, R5.1, U1.7 (OUT)
unnamed: C5.2, R16.1, R18.1, R20.1, U3.1 (OUT)
unnamed: C5.1, R16.2, R17.1, U3.2 (-IN)
unnamed: GUITAR_OUT.P$1_TIP (TIP), R20.2
unnamed: R18.2, T2.B
unnamed: R19.2, T2.E
unnamed: LED1.K (C), T2.C
unnamed: R33.2, T5.E
unnamed: LED4.K (C), T5.C
unnamed: GUITAR_POT.3 (E), LB_B.P$1
unnamed: GUITAR_POT.2 (S), U3.3 (+IN)
V+: U1.4 (V+), U3.8 (V+)
V-: U1.11 (V-), U3.4 (V-)

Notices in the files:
chrisEurorack/mains/mains_expander.brd:
CC BY-SA License
parts and their libraries:
SparkFun-PowerIC: Licensing: Creative Commons ShareAlike 4.0 International - https://creativecommons.org/licenses/by-sa/4.0
